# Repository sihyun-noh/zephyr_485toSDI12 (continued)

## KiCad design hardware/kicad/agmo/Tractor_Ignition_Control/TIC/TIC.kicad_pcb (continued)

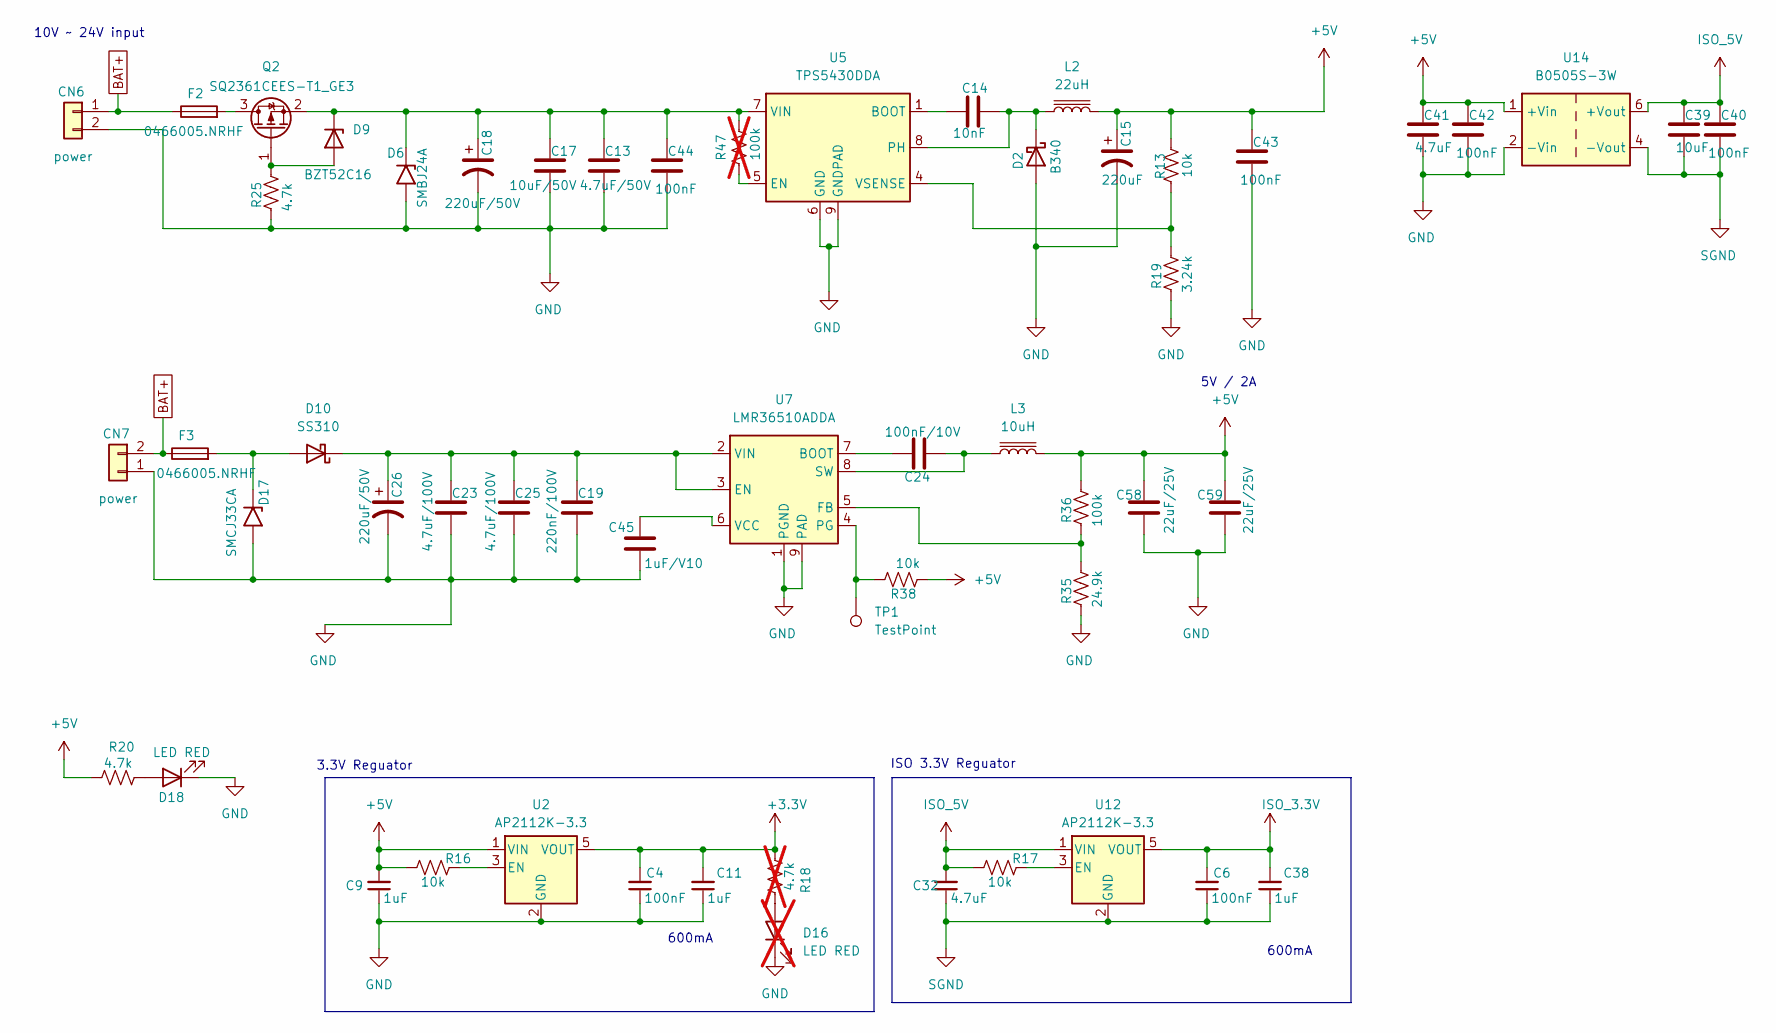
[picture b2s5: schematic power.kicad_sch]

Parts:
C4, C6: 100nF; R_0805_2012Metric_Pad1.20x1.40mm_HandSolder
C9, C11, C38: 1uF; R_0805_2012Metric_Pad1.20x1.40mm_HandSolder
C13: 4.7uF/50V; C_1812_4532Metric
C14: 10nF; C_0805_2012Metric_Pad1.18x1.45mm_HandSolder
C15: 220uF; CP_EIA-7343-31_Kemet-D; LCSC C130380
C17: 10uF/50V; C_1812_4532Metric
C18, C26: 220uF/50V; CP_Elec_10x10; LCSC C125976
C19: 220nF/100V; C_0603_1608Metric
C23, C25: 4.7uF/100V; C_1210_3225Metric
C24: 100nF/10V; C_0805_2012Metric_Pad1.18x1.45mm_HandSolder
C32: 4.7uF; R_0805_2012Metric_Pad1.20x1.40mm_HandSolder
C39: 10uF; C_0805_2012Metric_Pad1.18x1.45mm_HandSolder; LCSC C1779
C40, C42, C43: 100nF; C_0805_2012Metric_Pad1.18x1.45mm_HandSolder; LCSC C1779
C41: 4.7uF; C_0805_2012Metric_Pad1.18x1.45mm_HandSolder; LCSC C1779
C44: 100nF; C_0805_2012Metric
C45: 1uF/V10; C_0805_2012Metric
C58, C59: 22uF/25V; C_0805_2012Metric_Pad1.18x1.45mm_HandSolder
CN6, CN7: power; PhoenixContact_MSTBA_2,5_2-G-5,08_1x02_P5.08mm_Horizontal; LCSC C395737
D2: B340; D_SMB; LCSC C3018525
D6: SMBJ24A; D_SMA; LCSC C224017
D9: BZT52C16; D_SOD-123
D10: SS310; D_SMA
D16: LED RED; LED_0805_2012Metric; not fitted
D17: SMCJ33CA; D_SMC; LCSC C224017
D18: LED RED; LED_0805_2012Metric
F2, F3: 0466005.NRHF; Fuse_1206_3216Metric_Pad1.42x1.75mm_HandSolder; LCSC C57525
L2: 22uH; L_APV_APH0630; LCSC C5349702
L3: 10uH; L_APV_APH0630
Q2: SQ2361CEES-T1_GE3; SOT-23; LCSC C29267586
R13, R16, R17, R38: 10k; R_0805_2012Metric
R18: 4.7k; R_0805_2012Metric; not fitted
R19: 3.24k; R_0805_2012Metric
R20, R25: 4.7k; R_0805_2012Metric
R35: 24.9k; R_0805_2012Metric
R36: 100k; R_0805_2012Metric
R47: 100k; R_0805_2012Metric; not fitted
TP1: TestPoint
U2, U12: AP2112K-3.3; SOT-23-5; LCSC C51118
U5: TPS5430DDA; TI_SO-PowerPAD-8_ThermalVias; LCSC C9864
U7: LMR36510ADDA; Texas_HTSOP-8-1EP_3.9x4.9mm_P1.27mm_EP2.95x4.9mm_Mask2.4x3.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
U14: B0505S-3W; Converter_DCDC_TRACO_TBA2-xxxx_Single_THT; LCSC C7465195

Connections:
+3.3V: C4.2, C11.2, R18.2, U2.5 (VOUT); also elsewhere on the board
+5V: C9.2, C15.1, C41.1, C42.1, C43.1, C58.1, C59.1, L2.2, L3.2, R13.1, R16.1, R20.2, R36.1, R38.2, U2.1 (VIN), U14.1 (+Vin); also elsewhere on the board
ISO_3.3V: C6.2, C38.2, U12.5 (VOUT); also elsewhere on the board
ISO_5V: C32.2, C39.1, C40.1, R17.1, U12.1 (VIN), U14.6 (+Vout); also elsewhere on the board
unnamed: C14.2, D2.1 (K), L2.1, U5.8 (PH)
unnamed: C13.1, C17.1, C18.1, C44.1, D6.1 (A1), D9.1 (K), Q2.2 (S), R47.2, U5.7 (VIN)
unnamed: D9.2 (A), Q2.1 (G), R25.1
unnamed: D10.2 (A), D17.1 (A1), F3.2
unnamed: C19.1, C23.1, C25.1, C26.1, D10.1 (K), U7.2 (VIN), U7.3 (EN)
unnamed: D16.2 (A), R18.1
unnamed: D18.2 (A), R20.1
unnamed: F2.2, Q2.3 (D)
unnamed: R16.2, U2.3 (EN)
unnamed: C14.1, U5.1 (BOOT)
unnamed: R47.1, U5.5 (EN)
unnamed: R13.2, R19.1, U5.4 (VSENSE)
unnamed: C24.2, U7.7 (BOOT)
unnamed: R35.1, R36.2, U7.5 (FB)
unnamed: R38.1, TP1.1, U7.4 (PG)
unnamed: C24.1, L3.1, U7.8 (SW)
unnamed: C45.1, U7.6 (VCC)
unnamed: R17.2, U12.3 (EN)
SGND: C6.1, C32.1, C38.1, C39.2, C40.2, U12.2 (GND), U14.4 (-Vout); also elsewhere on the board

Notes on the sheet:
3.3V Reguator
600mA
5V / 2A
ISO 3.3V Reguator
10V ~ 24V input

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
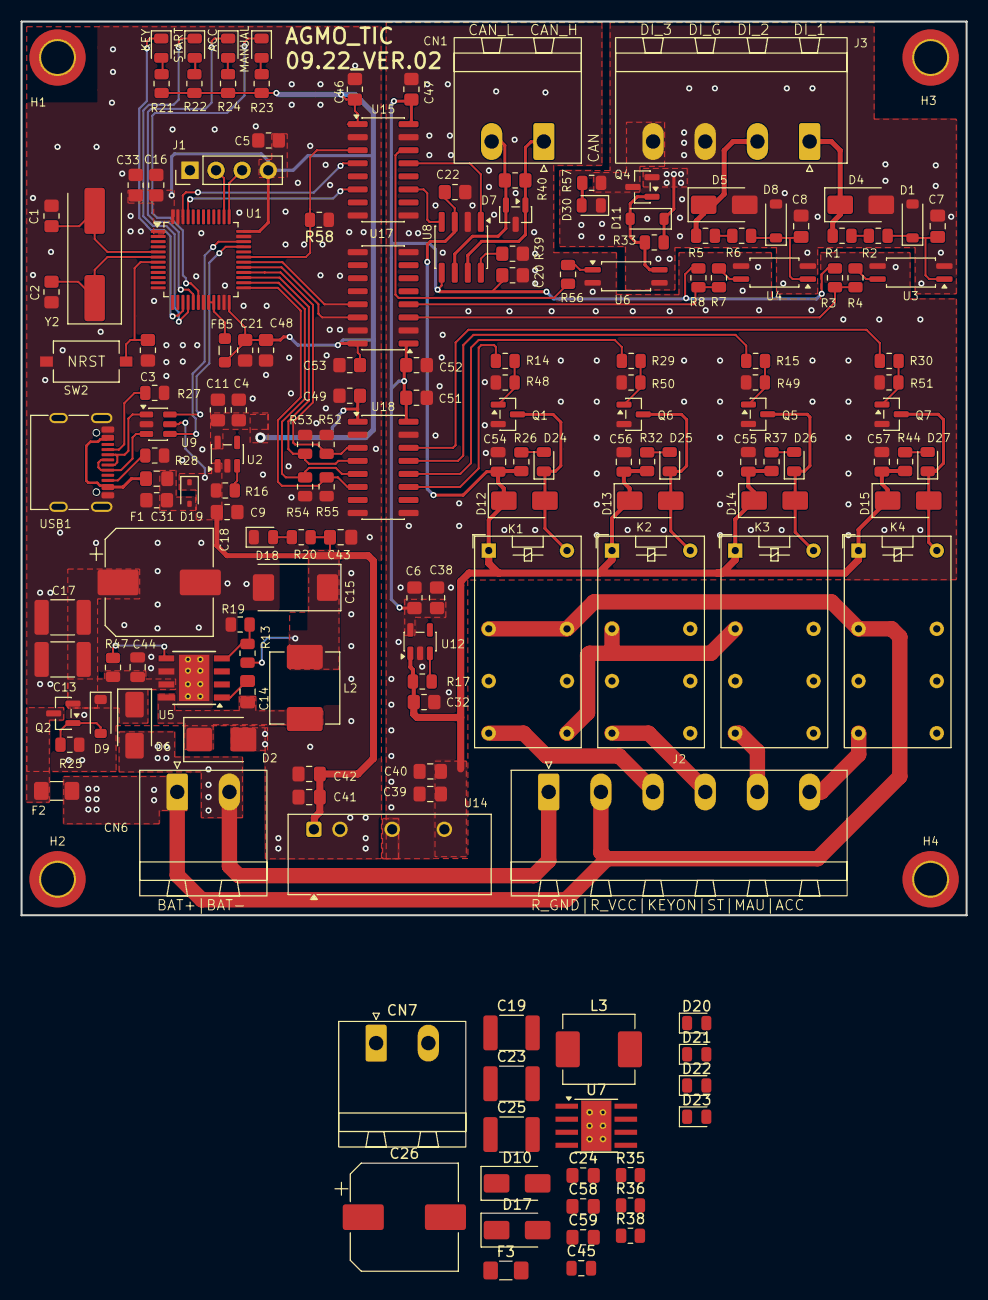
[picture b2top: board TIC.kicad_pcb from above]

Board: 2 copper layers, 92.0 x 87.0 mm, 167 parts (0 on the bottom side), 97 nets.

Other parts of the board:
ACC: LED RED; LED_0805_2012Metric
KEY: LED RED; LED_0805_2012Metric
MANUAL: LED RED; LED_0805_2012Metric
START: LED RED; LED_0805_2012Metric

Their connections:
/MCU/ACC_LED: ACC.1 (K); also elsewhere on the board
/MCU/KEYON_LED: KEY.1 (K); also elsewhere on the board
/MCU/MANUAL_LED: MANUAL.1 (K); also elsewhere on the board
/MCU/RESTART_LED: START.1 (K); also elsewhere on the board
unnamed 55: KEY.2 (A); also elsewhere on the board
unnamed 56: START.2 (A); also elsewhere on the board
unnamed 57: MANUAL.2 (A); also elsewhere on the board
unnamed 58: ACC.2 (A); also elsewhere on the board

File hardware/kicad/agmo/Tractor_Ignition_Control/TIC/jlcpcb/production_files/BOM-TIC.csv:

Comment,Designator,Footprint,LCSC,Quantity
0466005.NRHF,F2,Fuse_1206_3216Metric_Pad1.42x1.75mm_HandSolder,C57525,1
100,"R14,R15,R29,R30,R4,R7",R_0805_2012Metric,C17408,6
100k,R47,R_0805_2012Metric,C149504,1
100nF,"C16,C20,C21,C22,C3,C31,C4,C40,C42,C43,C44,C46,C47,C49,C5,C51,C52,C53,C54,C55,C56,C57,C6",R_0805_2012Metric_Pad1.20x1.40mm_HandSolder,C28233,23
10k,"R13,R16,R17,R27,R28,R3,R52,R53,R54,R55,R8",R_0805_2012Metric,C17414,11
10nF,C14,C_0805_2012Metric_Pad1.18x1.45mm_HandSolder,C1710,1
10uF,C39,C_0805_2012Metric_Pad1.18x1.45mm_HandSolder,C15850,1
10uF/50V,C17,C_1812_4532Metric,C1021609,1
120,R40,R_0805_2012Metric_Pad1.20x1.40mm_HandSolder,C17437,1
1N4148W,"D1,D8",D_SOD-123,C2099,2
1N5819,D19,D_SOD-323,C191023,1
1uF,"C11,C33,C38,C48,C9",R_0805_2012Metric_Pad1.20x1.40mm_HandSolder,C28323,5
2.2k,"R26,R32,R37,R44",R_0805_2012Metric,C17520,4
220uF,C15,CP_EIA-7343-31_Kemet-D,C130380,1
220uF/50V,C18,CP_Elec_10x10,C125976,1
22nF,"C7,C8",C_0805_2012Metric_Pad1.18x1.45mm_HandSolder,C1729,2
22pF,"C1,C2",R_0805_2012Metric_Pad1.20x1.40mm_HandSolder,C1804,2
22uH,L2,L_APV_APH0630,C5349702,1
3.24k,R19,R_0805_2012Metric,C865459,1
4.7k,"R1,R2,R20,R21,R22,R23,R24,R25,R5,R6",R_0805_2012Metric,C17673,10
4.7uF,"C32,C41",R_0805_2012Metric_Pad1.20x1.40mm_HandSolder,C98195,2
4.7uF/50V,C13,C_1812_4532Metric,C24976,1
47k,"R48,R49,R50,R51",R_0805_2012Metric,C17713,4
600Ω @ 100MHz,FB5,L_0805_2012Metric_Pad1.05x1.20mm_HandSolder,C81034,1
8Mhz,Y2,Crystal_SMD_HC49-SD,C12674,1
AP2112K-3.3,"U12,U2",SOT-23-5,C51118,2
B0505S-3W,U14,Converter_DCDC_TRACO_TBA2-xxxx_Single_THT,C7465195,1
B340,D2,D_SMB,C3018525,1
BZT52C16,D9,D_SOD-123,C2105,1
CAN,CN1,"PhoenixContact_MSTBA_2,5_2-G-5,08_1x02_P5.08mm_Horizontal",C395737,1
G5V-2-H1,"K1,K2,K3,K4",Relay_DPDT_Omron_G5V-2,C28066,4
IRLML6344,"Q1,Q5,Q6,Q7",SOT-23,C53550,4
LED RED,D18,LED_0805_2012Metric,C2295,1
LED RED,"ACC,D24,D25,D26,D27,KEY,MANUAL,START",LED_0805_2012Metric,C2297,8
MF-PSMF050X-2,F1,C_0805_2012Metric_Pad1.18x1.45mm_HandSolder,C116170,1
NRST,SW2,SW_Tactile_SPST_NO_Straight_CK_PTS636Sx25SMTRLFS,C42420257,1
SM24CANB-02HTG,D7,SOT-23,C151237,1
SMAJ33A,"D4,D5",D_SMA,C223988,2
SMBJ24A,D6,D_SMA,C224017,1
SQ2361CEES-T1_GE3,"Q2,Q4",SOT-23,C29267586,2
SS14,"D12,D13,D14,D15",D_SMA,C2480,4
STM32G431C8Tx,U1,LQFP-48_7x7mm_P0.5mm,C730096,1
Screw_Terminal_01x04,J3,"PhoenixContact_MSTBA_2,5_4-G-5,08_1x04_P5.08mm_Horizontal",C395753,1
Screw_Terminal_01x06,J2,"PhoenixContact_MSTBA_2,5_6-G-5,08_1x06_P5.08mm_Horizontal",C395769,1
TJA1051T-3,U8,SOIC-8_3.9x4.9mm_P1.27mm,C38695,1
TLP293,"U3,U4,U6",SOIC-4_4.55x2.6mm_P1.27mm,C77656,3
TPS5430DDA,U5,TI_SO-PowerPAD-8_ThermalVias,C9864,1
USBLC6-2SC6,U9,SOT-23-6,C2827654,1
USB_C_Receptacle_USB2.0_16P,USB1,USB_C_Receptacle_G-Switch_GT-USB-7010ASV,C2988369,1
power,CN6,"PhoenixContact_MSTBA_2,5_2-G-5,08_1x02_P5.08mm_Horizontal",C395737,1
π140U31,"U17,U18",SOIC-16_3.9x9.9mm_P1.27mm,C471601,2
π142M31,U15,SOIC-16_3.9x9.9mm_P1.27mm,C471606,1
Debug,J1,PinHeader_1x04_P2.54mm_Vertical,,1
BZT52C16,D11,D_SOD-123,,1
0/J,R39,R_0805_2012Metric_Pad1.20x1.40mm_HandSolder,,1
10k,R58,R_0805_2012Metric,,1
47k,R33,R_0805_2012Metric,,1
4.7k,R57,R_0805_2012Metric,,1
LED RED,D30,LED_0805_2012Metric,,1
1k,R56,R_0805_2012Metric,,1

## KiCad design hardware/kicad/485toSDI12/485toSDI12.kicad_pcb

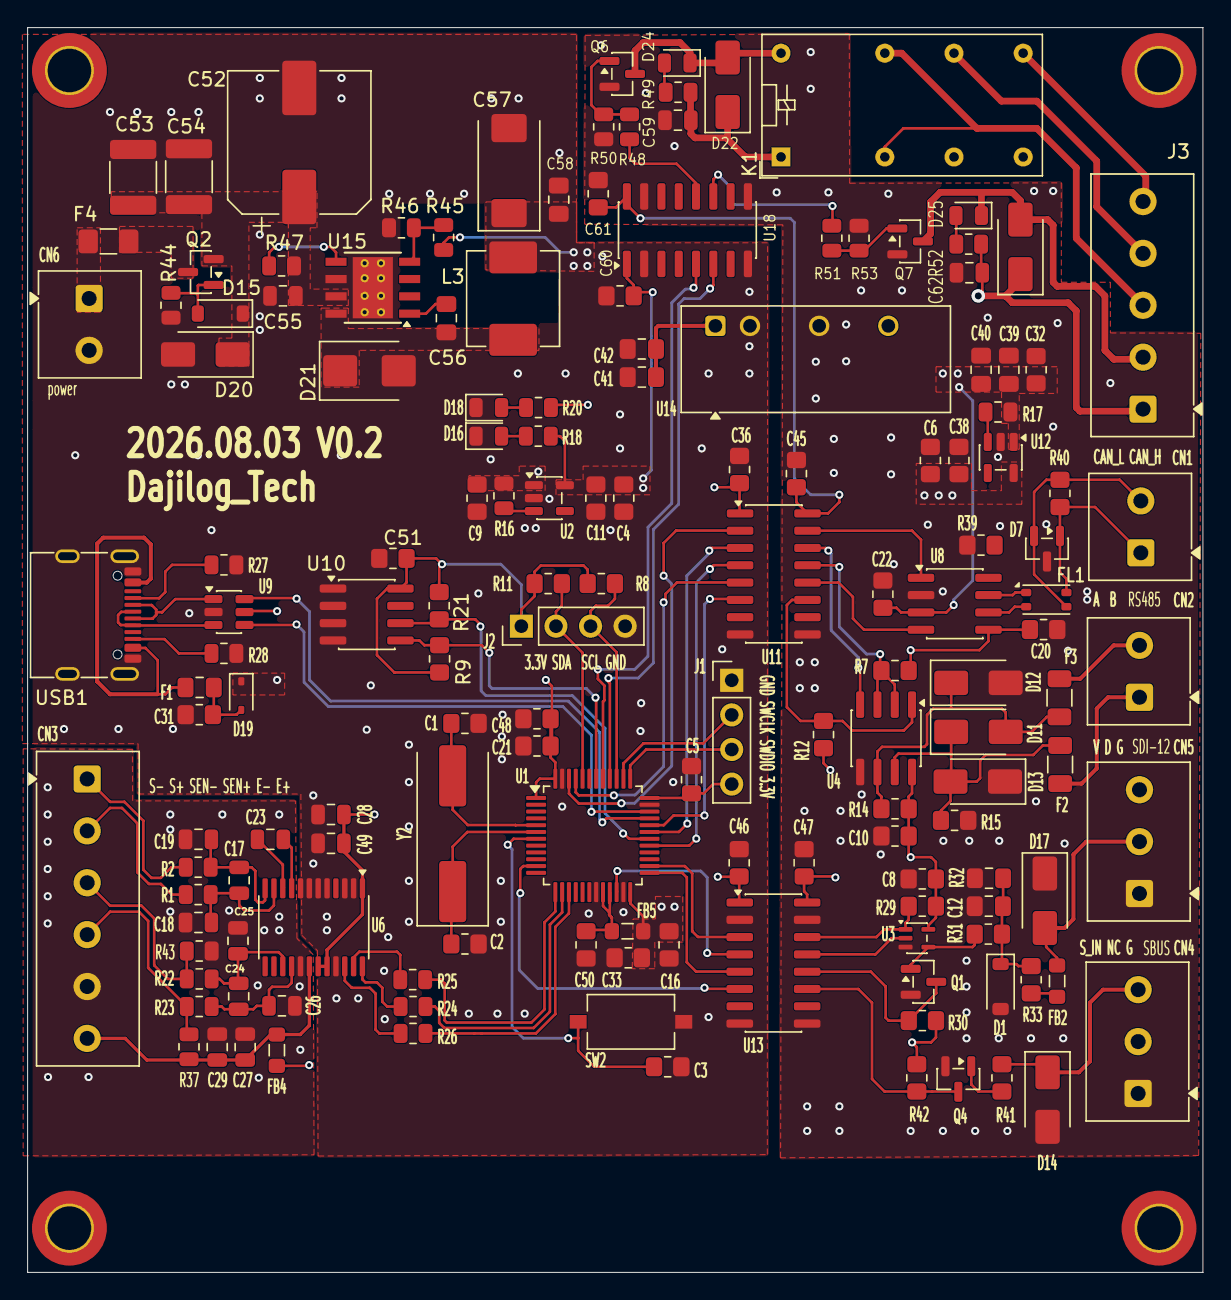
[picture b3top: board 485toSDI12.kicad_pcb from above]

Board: 4 copper layers, 86.3 x 91.4 mm, 156 parts (0 on the bottom side), 99 nets.

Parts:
C1, C2: 22pF; R_0805_2012Metric_Pad1.20x1.40mm_HandSolder
C3, C4, C5, C6, C8, C16, C20, C21, C22, C31, C36, C45, C46, C47, C51, C60, C61: 100nF; R_0805_2012Metric_Pad1.20x1.40mm_HandSolder
C9, C11, C33, C38, C48, C50: 1uF; R_0805_2012Metric_Pad1.20x1.40mm_HandSolder
C10: 100nF/50V; R_0805_2012Metric_Pad1.20x1.40mm_HandSolder
C12, C56: 10nF; C_0805_2012Metric_Pad1.18x1.45mm_HandSolder
C17: 47nF; C_0805_2012Metric
C18, C19: 4.7nF; C_0805_2012Metric
C23, C27, C28, C55, C59, C62: 100nF; C_0805_2012Metric
C24, C49: 1uF; C_0805_2012Metric
C25, C26, C29: 10nF; C_0805_2012Metric
C32: 4.7uF; R_0805_2012Metric_Pad1.20x1.40mm_HandSolder
C39: 10uF; C_0805_2012Metric_Pad1.18x1.45mm_HandSolder
C40, C42, C58: 100nF; C_0805_2012Metric_Pad1.18x1.45mm_HandSolder
C41: 4.7uF; C_0805_2012Metric_Pad1.18x1.45mm_HandSolder
C52: 220uF/50V; CP_Elec_10x10
C53: 10uF/50V; C_1812_4532Metric
C54: 4.7uF/50V; C_1812_4532Metric
C57: 220uF; CP_EIA-7343-31_Kemet-D
CN1: CAN; TerminalBlock_Phoenix_MKDS-1-2-3.81_1x02_P3.81mm_Horizontal
CN2: RS485; TerminalBlock_Phoenix_MKDS-1-2-3.81_1x02_P3.81mm_Horizontal
CN3: L/C; TerminalBlock_Phoenix_MKDS-1-6-3.81_1x06_P3.81mm_Horizontal
CN4: SBUS; TerminalBlock_Phoenix_MKDS-1-3-3.81_1x03_P3.81mm_Horizontal
CN5: SDI-12; TerminalBlock_Phoenix_MKDS-1-3-3.81_1x03_P3.81mm_Horizontal
CN6: power; TerminalBlock_Phoenix_MKDS-1-2-3.81_1x02_P3.81mm_Horizontal
D1: BZT52B5V6; D_SOD-123
D7: SM24CANB-02HTG; SOT-23
D11, D12, D13, D14, D17: SMAJ12CA; D_SMA
D15: BZT52C16; D_SOD-123
D16, D18, D24, D25: LED RED; LED_0805_2012Metric
D19: 1N5819; D_SOD-323
D20: SMBJ24A; D_SMA
D21: B340; D_SMB
D22, D23: SS14; D_SMA
F1: MF-PSMF050X-2; C_0805_2012Metric_Pad1.18x1.45mm_HandSolder
F2, F3: BSMD1206-020-30V; Fuse_1206_3216Metric
F4: 0466005.NRHF; Fuse_1206_3216Metric_Pad1.42x1.75mm_HandSolder
FB2, FB4: 300Ω@100MHz; L_0805_2012Metric_Pad1.05x1.20mm_HandSolder
FB5: 600Ω @ 100MHz; L_0805_2012Metric_Pad1.05x1.20mm_HandSolder
FL1: ACT45B-510-2P-TL003; L_CommonModeChoke_Coilank_ACM3216
H1, H2, H3, H4: MountingHole; MountingHole_3.2mm_M3_ISO14580_Pad_TopBottom
J1: Debug; PinHeader_1x04_P2.54mm_Vertical
J2: I2C; PinHeader_1x04_P2.54mm_Vertical
J3: Screw_Terminal_01x05; TerminalBlock_Phoenix_MKDS-1-5-3.81_1x05_P3.81mm_Horizontal
K1: G5V-2-H1; Relay_DPDT_Omron_G5V-2
L3: 22uH; L_APV_APH0630
Q1: 2N7002; SOT-23
Q2: SQ2361CEES-T1_GE3; SOT-23
Q4: MMBT4401; SOT-23
Q6, Q7: IRLML6344; SOT-23
R1, R2, R22, R23: 100 / B 25ppm; R_0805_2012Metric
R7, R8, R9, R11, R12, R21, R30: 4.7K/J; R_0805_2012Metric_Pad1.20x1.40mm_HandSolder
R14, R15, R42: 10K/J; R_0805_2012Metric_Pad1.20x1.40mm_HandSolder
R16, R17, R27, R28: 10K/J; R_0805_2012Metric
R18, R20: 4.7K/J; R_0805_2012Metric
R24, R25, R26: 47/J; R_0805_2012Metric
R29: 47K/J; R_0805_2012Metric_Pad1.20x1.40mm_HandSolder
R31, R33: 510/J; R_0805_2012Metric_Pad1.20x1.40mm_HandSolder
R32: 200K/J; C_0805_2012Metric_Pad1.18x1.45mm_HandSolder
R37, R43: 0 / J; R_0805_2012Metric
R39: 0/J; R_0805_2012Metric_Pad1.20x1.40mm_HandSolder
R40: 120/J; R_0805_2012Metric_Pad1.20x1.40mm_HandSolder
R41: 1K/J; R_0805_2012Metric_Pad1.20x1.40mm_HandSolder
R44: 4.7k; R_0805_2012Metric
R45: 10k; R_0805_2012Metric
R46: 3.24k; R_0805_2012Metric
R47: 100k; R_0805_2012Metric
R48, R51: 100; R_0805_2012Metric
R49, R52: 2.2k; R_0805_2012Metric
R50, R53: 47k; R_0805_2012Metric
SW2: NRST; SW_Tactile_SPST_NO_Straight_CK_PTS636Sx25SMTRLFS
U1: STM32G431C8Tx; LQFP-48_7x7mm_P0.5mm
U2, U12: AP2112K-3.3; SOT-23-5
U3: 74LVC1G125SE-7; SOT-353_SC-70-5
U4: SP3485EN; SOIC-8_3.9x4.9mm_P1.27mm
U6: ADS1232IPW; TSSOP-24_4.4x7.8mm_P0.65mm
U8: TJA1051T-3; SOIC-8_3.9x4.9mm_P1.27mm
U9: USBLC6-2SC6; SOT-23-6
U10: AT24C256C-SSHL; SOIC-8_3.9x4.9mm_P1.27mm
U11: π163E31; SOIC-16_3.9x9.9mm_P1.27mm
U13: π142M31; SOIC-16_3.9x9.9mm_P1.27mm
U14: B0505S-2W; Converter_DCDC_TRACO_TBA2-xxxx_Single_THT
U15: TPS5430DDA; TI_SO-PowerPAD-8_ThermalVias
U18: π140U31; SOIC-16_3.9x9.9mm_P1.27mm
USB1: USB_C_Receptacle_USB2.0_16P; USB_C_Receptacle_G-Switch_GT-USB-7010ASV
Y2: 8Mhz; Crystal_SMD_HC49-SD

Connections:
485_EN: U1.29 (PB15), U11.4 (A3)
+3.3V: C4.2, C5.2, C11.2, C16.2, C21.2, C33.2, C36.1, C46.1, C48.2, C51.1, C60.1, FB5.1, J1.4, J2.1, R8.1, R9.1, R11.1, R18.2, R21.1, U1.1 (VBAT), U1.24 (VDD), U1.36 (VDD), U1.48 (VDD), U2.5 (VOUT), U10.8 (VCC), U11.1 (VDD1), U13.1 (VDD1), U18.1 (VDD1)
+3.3VA: C50.2, FB5.2, U1.20 (VREF+), U1.21 (VDDA)
+5V: C9.2, C28.1, C41.1, C42.1, C49.1, C57.1, C58.1, D19.1 (K), FB4.2, L3.2, R16.1, R20.2, R45.1, U2.1 (VIN), U6.1 (DVDD), U6.19 (GAIN0), U6.20 (GAIN1), U9.5 (VBUS), U14.1 (+Vin)
+5VA: C27.1, C29.1, CN3.6, FB4.1, R37.1, U6.18 (AVDD)
/ADC, CURRENT_LOOP/SEN+: CN3.4, R23.2, R37.2
/ADC, CURRENT_LOOP/SEN-: CN3.3, R22.2, R43.2
/Relay_out Sheet/ISO_DO1: R48.1, U18.12 (B3)
/Relay_out Sheet/ISO_DO2: R51.1, U18.11 (B4)
/interface-sdi12-sbus/ISO_OE: R29.2, U3.1 (~OE), U13.14 (B1)
/interface-sdi12-sbus/ISO_SBUS: Q4.3 (C), R42.2, U13.11 (B4)
/interface-sdi12-sbus/ISO_SDI12_RXD: Q1.3 (D), R30.2, U13.12 (B3)
/interface-sdi12-sbus/ISO_SDI12_TXD: U3.2 (A), U13.13 (B2)
/interface-sdi12-sbus/SBUS_IN: CN4.3, D14.1 (A1), R41.2
/interface/CAN_H: CN1.1, D7.1 (A1), FL1.4, R40.1
/interface/CAN_L: CN1.2, D7.2 (A2), FL1.3, R40.2
/interface/ISO_485_EN: R7.2, U4.2 (~RE), U4.3 (DE), U11.13 (B3)
/interface/ISO_485_RXD: R12.2, U4.1 (RO), U11.11 (B5)
/interface/ISO_485_TXD: U4.4 (DI), U11.14 (B2)
/interface/ISO_CAN_RXD: U8.4 (RXD), U11.12 (B4)
/interface/ISO_CAN_TXD: U8.1 (TXD), U11.15 (B1)
A: CN2.2, F3.2
B: CN2.1, F2.2
CANFD_RX: U1.45 (PB8), U11.5 (A4)
CANFD_TX: U1.46 (PB9), U11.2 (A1)
DO1: U1.41 (PB4), U18.5 (A3)
DO2: U1.40 (PB3), U18.6 (A4)
GND: C1.1, C2.1, C3.1, C4.1, C5.1, C9.1, C11.1, C16.1, C18.2, C19.1, C21.1, C25.1, C26.2, C27.2, C28.2, C29.2, C31.1, C33.1, C36.2, C41.2, C42.2, C46.2, C48.1, C49.2, C50.1, C51.2, C52.2, C53.2, C54.2, C55.2, C57.2, C58.2, C60.2, CN3.5, CN6.2, D16.1 (K), D18.1 (K), D20.2 (A2), D21.2 (A), J1.1, J2.4, R27.2, R28.2, R43.1, R44.2, R46.2, SW2.1, U1.19 (VSSA), U1.23 (VSS), U1.35 (VSS), U1.47 (VSS), U2.2 (GND), U6.2 (DGND), U6.3 (CLKIN/XTAL1), U6.5 (DGND), U6.6 (DGND), U6.7 (TEMP), U6.8 (A0), U6.17 (AGND), U6.21 (SPEED), U9.2 (GND), U10.1 (A0), U10.2 (A1), U10.3 (A2), U10.4 (GND), U11.8 (GND1), U13.2 (GND1), U13.8 (GND1), U14.2 (-Vin), U15.6 (GND), U15.9 (GNDPAD), U18.2 (GND1), U18.8 (GND1), USB1.A1 (GND), USB1.A12 (GND), USB1.B1 (GND), USB1.B12 (GND), USB1.SH (SHIELD)
I2C1_SCL: J2.3, R8.2, U1.39 (PA15)
I2C1_SDA: J2.2, R11.2, U1.44 (PB7)
I2C3_SCL: R21.2, U1.30 (PA8), U10.6 (SCL)
I2C3_SDA: R9.2, U1.42 (PB5), U10.5 (SDA)
ISO_3.3V: C6.2, C8.1, C10.1, C20.1, C38.2, C45.2, C47.1, C61.1, R7.1, R12.1, R14.2, R29.1, R30.1, R42.1, U3.5 (VCC), U4.8 (VCC), U8.5 (VIO), U11.16 (VDD2), U12.5 (VOUT), U13.16 (VDD2), U18.16 (VDD2)
ISO_5V: C22.1, C32.2, C39.1, C40.1, C59.1, C62.1, D22.1 (K), D23.1 (K), J3.1, K1.1, R17.1, R49.1, R52.1, U8.3 (VCC), U12.1 (VIN), U14.6 (+Vout)
unnamed: C23.1, U6.9 (CAP)
unnamed: C23.2, U6.10 (CAP)
unnamed: CN6.1, F4.1
unnamed: C12.1, D1.1 (K), R31.2, R32.2, R33.1
unnamed: D11.1 (A1), D13.2 (A2), F2.1, R15.2, U4.7 (B)
unnamed: D11.2 (A2), D12.1 (A1), F3.1, R14.1, U4.6 (A)
unnamed: D15.2 (A), Q2.1 (G), R44.1
unnamed: C52.1, C53.1, C54.1, C55.1, D15.1 (K), D20.1 (A1), Q2.2 (S), R47.2, U15.7 (VIN)
unnamed: D16.2 (A), R18.1
unnamed: D18.2 (A), R20.1
unnamed: C31.2, D19.2 (A), F1.2
unnamed: C56.2, D21.1 (K), L3.1, U15.8 (PH)
unnamed: D22.2 (A), D24.1 (K), K1.16, Q6.3 (D)
unnamed: D23.2 (A), D25.1 (K), J3.2, Q7.3 (D)
unnamed: D24.2 (A), R49.2
unnamed: D25.2 (A), R52.2
unnamed: FB2.1, R33.2
unnamed: J3.3, K1.4, K1.13
unnamed: J3.4, K1.11
unnamed: J3.5, K1.9
unnamed: Q1.1 (G), R31.1, U3.4 (Y)
unnamed: F4.2, Q2.3 (D)
unnamed: Q4.1 (B), R41.1
unnamed: Q6.1 (G), R48.2, R50.2
unnamed: Q7.1 (G), R51.2, R53.2
unnamed: C3.2, SW2.2, U1.7 (PG10-NRST)
unnamed: R16.2, U2.3 (EN)
unnamed: C17.2, C19.2, R2.1, U6.12 (AINN1)
unnamed: C17.1, C18.1, R1.1, U6.11 (AINP1)
unnamed: C24.2, C25.2, R22.1, U6.15 (REFN)
unnamed: C24.1, C26.1, R23.1, U6.16 (REFP)
unnamed: R25.1, U6.23 (SCLK)
unnamed: R24.1, U6.24 (~DRDY/DOUT)
unnamed: R26.1, U6.22 (~PWDN)
unnamed: FL1.1, U8.7 (CANH)
unnamed: FL1.2, U8.6 (CANL)
unnamed: R39.2, U8.8 (S)
unnamed: U9.1 (I/O1), USB1.A7 (D-), USB1.B7 (D-)
unnamed: U9.3 (I/O2), USB1.A6 (D+), USB1.B6 (D+)
unnamed: R17.2, U12.3 (EN)
unnamed: C56.1, U15.1 (BOOT)
unnamed: R47.1, U15.5 (EN)
unnamed: R45.2, R46.1, U15.4 (VSENSE)
unnamed: R27.1, USB1.A5 (CC1)
unnamed: R28.1, USB1.B5 (CC2)
OE: U1.26 (PB12), U13.3 (A1)
OSC_IN: C1.2, U1.5 (PF0), Y2.2
OSC_OUT: C2.2, U1.6 (PF1), Y2.1
RXD1: U1.32 (PA10), U11.6 (A5)
RXD2: U1.11 (PA3), U13.6 (A4)
RXD3: U1.25 (PB11), U13.5 (A3)
SDI12_Data: CN5.2, D17.2 (A2), FB2.2
SGND: C6.1, C8.2, C10.2, C12.2, C20.2, C22.2, C32.1, C38.1, C39.2, C40.2, C45.1, C47.2, C59.2, C61.2, C62.2, CN4.1, CN5.1, D1.2 (A), D7.3 (common), D12.2 (A2), D13.1 (A1), D14.2 (A2), D17.1 (A1), Q1.2 (S), Q4.2 (E), Q6.2 (S), Q7.2 (S), R15.1, R32.1, R39.1, R50.1, R53.1, U3.3 (GND), U4.5 (GND), U8.2 (GND), U11.9 (GND2), U12.2 (GND), U13.9 (GND2), U13.15 (GND2), U14.4 (-Vout), U18.9 (GND2), U18.15 (GND2)
SPI_DOUT: R24.2, U1.14 (PA6)
SPI_PWDN: R26.2, U1.15 (PA7)
SPI_SCLK: R25.2, U1.13 (PA5)
SWCLK: J1.2, U1.38 (PA14)
SWDIO: J1.3, U1.37 (PA13)
TXD1: U1.31 (PA9), U11.3 (A2)
TXD3: U1.22 (PB10), U13.4 (A2)
USB D+: U1.34 (PA12), U9.4 (I/O2)
USB D-: U1.33 (PA11), U9.6 (I/O1)
VUSB: F1.1, USB1.A4 (VBUS), USB1.A9 (VBUS), USB1.B4 (VBUS), USB1.B9 (VBUS)
s+: CN3.2, R1.2
s-: CN3.1, R2.2

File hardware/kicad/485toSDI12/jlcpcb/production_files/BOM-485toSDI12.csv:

Comment,Designator,Footprint,LCSC,Quantity
0 / J,"R37,R43",R_0805_2012Metric,C110773,2
0/J,R39,R_0805_2012Metric_Pad1.20x1.40mm_HandSolder,C17477,1
0466005.NRHF,F4,Fuse_1206_3216Metric_Pad1.42x1.75mm_HandSolder,C57525,1
100 / B 25ppm,"R1,R2,R22,R23",R_0805_2012Metric,C110773,4
100nF,"C16,C20,C21,C22,C23,C27,C28,C3,C31,C36,C4,C40,C42,C45,C46,C47,C5,C6,C8",R_0805_2012Metric_Pad1.20x1.40mm_HandSolder,C1711,19
100nF,C58,C_0805_2012Metric_Pad1.18x1.45mm_HandSolder,C1779,1
100nF/50V,C10,R_0805_2012Metric_Pad1.20x1.40mm_HandSolder,C1711,1
10K/J,"R14,R15,R16,R17,R27,R28,R42",R_0805_2012Metric_Pad1.20x1.40mm_HandSolder,C17414,7
10nF,"C12,C25,C26,C29",C_0805_2012Metric_Pad1.18x1.45mm_HandSolder,C1710,4
10uF,C39,C_0805_2012Metric_Pad1.18x1.45mm_HandSolder,C440198,1
120/J,R40,R_0805_2012Metric_Pad1.20x1.40mm_HandSolder,C17437,1
1K/J,R41,R_0805_2012Metric_Pad1.20x1.40mm_HandSolder,C17513,1
1N5819,D19,D_SOD-323,C191023,1
1uF,C49,C_0805_2012Metric,C1711,1
1uF,"C11,C24,C33,C38,C48,C50,C9",R_0805_2012Metric_Pad1.20x1.40mm_HandSolder,C28323,7
200K/J,R32,C_0805_2012Metric_Pad1.18x1.45mm_HandSolder,C105577,1
220uF,C57,CP_EIA-7343-31_Kemet-D,C130380,1
220uF/50V,C52,CP_Elec_10x10,C125976,1
22pF,"C1,C2",R_0805_2012Metric_Pad1.20x1.40mm_HandSolder,C1804,2
22uH,L3,L_APV_APH0630,C5349702,1
2N7002,Q1,SOT-23,C916396,1
300Ω@100MHz,"FB2,FB4",L_0805_2012Metric_Pad1.05x1.20mm_HandSolder,C2661775,2
4.7K/J,"R11,R12,R18,R20,R30,R7,R8",R_0805_2012Metric_Pad1.20x1.40mm_HandSolder,C865532,7
4.7nF,"C18,C19",C_0805_2012Metric,C1744,2
4.7uF,"C32,C41",R_0805_2012Metric_Pad1.20x1.40mm_HandSolder,C1779,2
47/J,"R24,R25,R26",R_0805_2012Metric,C17714,3
47K/J,R29,R_0805_2012Metric_Pad1.20x1.40mm_HandSolder,C105577,1
47nF,C17,C_0805_2012Metric,C53134,1
510/J,"R31,R33",R_0805_2012Metric_Pad1.20x1.40mm_HandSolder,C105577,2
600Ω @ 100MHz,FB5,L_0805_2012Metric_Pad1.05x1.20mm_HandSolder,C81034,1
74LVC1G125SE-7,U3,SOT-353_SC-70-5,C151022,1
8Mhz,Y2,Crystal_SMD_HC49-SD,C12674,1
ADS1232IPW,U6,TSSOP-24_4.4x7.8mm_P0.65mm,C27919,1
AP2112K-3.3,"U12,U2",SOT-23-5,C51118,2
AT24C256C-SSHL,U10,SOIC-8_3.9x4.9mm_P1.27mm,C6482,1
B0505S-2W,U14,Converter_DCDC_TRACO_TBA2-xxxx_Single_THT,C7465195,1
B340,D21,D_SMB,C3018525,1
BSMD1206-020-30V,"F2,F3",Fuse_1206_3216Metric,C883118,2
BZT52B5V6,D1,D_SOD-123,C2903913,1
CAN,CN1,TerminalBlock_Phoenix_MKDS-1-2-3.81_1x02_P3.81mm_Horizontal,C395878,1
IRLML6344,"Q6,Q7",SOT-23,C53550,2
L/C,CN3,TerminalBlock_Phoenix_MKDS-1-6-3.81_1x06_P3.81mm_Horizontal,C5143696,1
LED RED,"D16,D18",LED_0805_2012Metric,C84256,2
MF-PSMF050X-2,F1,C_0805_2012Metric_Pad1.18x1.45mm_HandSolder,C116170,1
MMBT4401,Q4,SOT-23,C31776,1
NRST,SW2,SW_Tactile_SPST_NO_Straight_CK_PTS636Sx25SMTRLFS,C42420257,1
RS485,CN2,TerminalBlock_Phoenix_MKDS-1-2-3.81_1x02_P3.81mm_Horizontal,C395878,1
SBUS,CN4,TerminalBlock_Phoenix_MKDS-1-3-3.81_1x03_P3.81mm_Horizontal,C395879,1
SDI-12,CN5,TerminalBlock_Phoenix_MKDS-1-3-3.81_1x03_P3.81mm_Horizontal,C395879,1
SM24CANB-02HTG,D7,SOT-23,C151237,1
SMAJ12CA,"D11,D12,D13,D14,D17",D_SMA,C83267,5
SMBJ24A,D20,D_SMA,C224017,1
SP3485EN,U4,SOIC-8_3.9x4.9mm_P1.27mm,C8963,1
SQ2361CEES-T1_GE3,Q2,SOT-23,C29267586,1
STM32G431C8Tx,U1,LQFP-48_7x7mm_P0.5mm,C529355,1
TJA1051T-3,U8,SOIC-8_3.9x4.9mm_P1.27mm,C38695,1
TPS5430DDA,U15,TI_SO-PowerPAD-8_ThermalVias,C9864,1
USBLC6-2SC6,U9,SOT-23-6,C2827654,1
USB_C_Receptacle_USB2.0_16P,USB1,USB_C_Receptacle_G-Switch_GT-USB-7010ASV,C2988369,1
power,CN6,TerminalBlock_Phoenix_MKDS-1-2-3.81_1x02_P3.81mm_Horizontal,C395878,1
π140U31,U18,SOIC-16_3.9x9.9mm_P1.27mm,C471601,1
π142M31,U13,SOIC-16_3.9x9.9mm_P1.27mm,C471606,1
π163E31,U11,SOIC-16_3.9x9.9mm_P1.27mm,C471613,1
Debug,J1,PinHeader_1x04_P2.54mm_Vertical,,1
I2C,J2,PinHeader_1x04_P2.54mm_Vertical,,1
100k,R47,R_0805_2012Metric,,1
3.24k,R46,R_0805_2012Metric,,1
4.7uF/50V,C54,C_1812_4532Metric,,1
4.7k,R44,R_0805_2012Metric,,1
10nF,C56,C_0805_2012Metric_Pad1.18x1.45mm_HandSolder,,1
100nF,C51,R_0805_2012Metric_Pad1.20x1.40mm_HandSolder,,1
10k,R45,R_0805_2012Metric,,1
BZT52C16,D15,D_SOD-123,,1
4.7K/J,R21,R_0805_2012Metric_Pad1.20x1.40mm_HandSolder,,1
4.7K/J,R9,R_0805_2012Metric_Pad1.20x1.40mm_HandSolder,,1
10uF/50V,C53,C_1812_4532Metric,,1
100nF,C55,C_0805_2012Metric,,1
Screw_Terminal_01x05,J3,TerminalBlock_Phoenix_MKDS-1-5-3.81_1x05_P3.81mm_Horizontal,,1
100,R51,R_0805_2012Metric,,1
2.2k,R52,R_0805_2012Metric,,1
47k,R53,R_0805_2012Metric,,1
100nF,C62,C_0805_2012Metric,,1
LED RED,D24,LED_0805_2012Metric,,1
47k,R50,R_0805_2012Metric,,1
2.2k,R49,R_0805_2012Metric,,1
100,R48,R_0805_2012Metric,,1
G5V-2-H1,K1,Relay_DPDT_Omron_G5V-2,,1
LED RED,D25,LED_0805_2012Metric,,1
SS14,D23,D_SMA,,1
SS14,D22,D_SMA,,1
100nF,C61,R_0805_2012Metric_Pad1.20x1.40mm_HandSolder,,1
100nF,C60,R_0805_2012Metric_Pad1.20x1.40mm_HandSolder,,1
100nF,C59,C_0805_2012Metric,,1

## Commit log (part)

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2026-06-04 Initial 485toSDI12 Zephyr application
